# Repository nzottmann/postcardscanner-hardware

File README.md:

## Hardware files for postcardscanner

License: CC-BY-SA-4.0

- 3D CAD, Fusion360 and STEP
- 3D printing files, 3MF
- Hardware BOM
- KiCAD files for custom PCB
- Pictures

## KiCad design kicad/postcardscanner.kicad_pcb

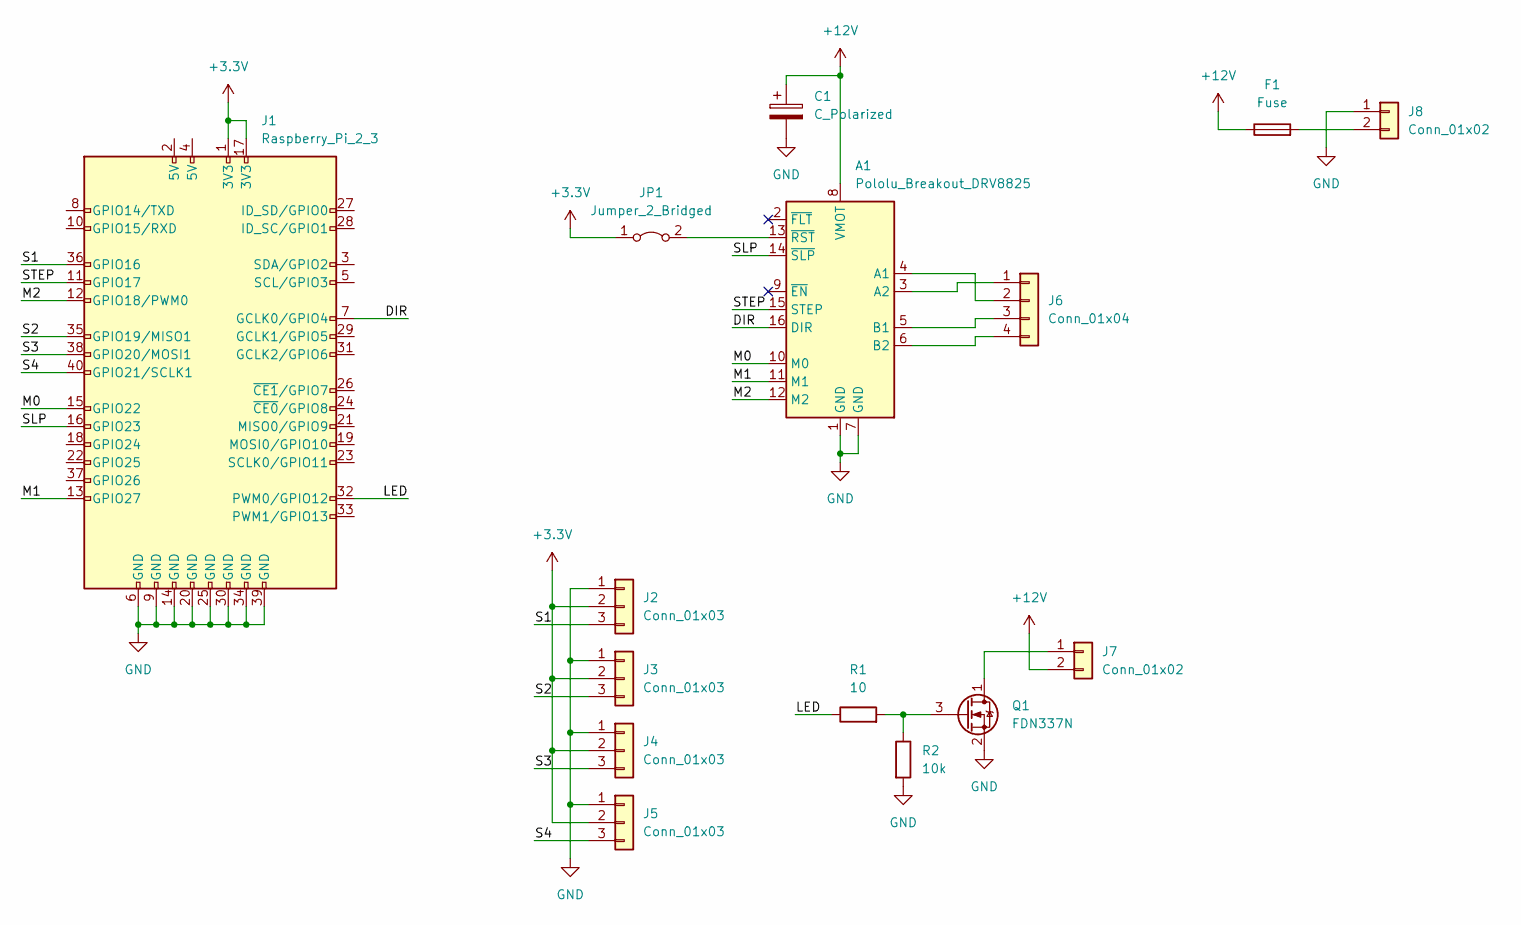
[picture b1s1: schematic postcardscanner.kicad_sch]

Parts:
A1: Pololu_Breakout_DRV8825; Pololu_Breakout-16_15.2x20.3mm
C1: C_Polarized; CP_Radial_D8.0mm_P5.00mm
F1: Fuse; Fuseholder_Littelfuse_445_030_series_5x20mm
J1: Raspberry_Pi_2_3; PinSocket_2x20_P2.54mm_Vertical
J2, J3, J4, J5: Conn_01x03; SolderWire-0.25sqmm_1x03_P4.2mm_D0.65mm_OD1.7mm_Relief
J6: Conn_01x04; SolderWire-0.25sqmm_1x04_P4.2mm_D0.65mm_OD1.7mm_Relief
J7: Conn_01x02; SolderWire-0.25sqmm_1x02_P4.2mm_D0.65mm_OD1.7mm_Relief
J8: Conn_01x02; SolderWire-0.5sqmm_1x02_P4.6mm_D0.9mm_OD2.1mm_Relief
JP1: Jumper_2_Bridged; SolderJumper-2_P1.3mm_Bridged_RoundedPad1.0x1.5mm
Q1: FDN337N; SOT-23_Handsoldering
R1: 10; R_0603_1608Metric_Pad0.98x0.95mm_HandSolder
R2: 10k; R_0603_1608Metric_Pad0.98x0.95mm_HandSolder

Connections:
+3.3V: J1.1 (3V3), J1.17 (3V3), J2.2, J3.2, J4.2, J5.2, JP1.1 (A)
+12V: A1.8 (VMOT), C1.1, F1.1, J7.2
/DIR: A1.16 (DIR), J1.7 (GCLK0/GPIO4)
/LED: J1.32 (PWM0/GPIO12), R1.1
/M0: A1.10 (M0), J1.15 (GPIO22)
/M1: A1.11 (M1), J1.13 (GPIO27)
/M2: A1.12 (M2), J1.12 (GPIO18/PWM0)
/S1: J1.36 (GPIO16), J2.3
/S2: J1.35 (GPIO19/MISO1), J3.3
/S3: J1.38 (GPIO20/MOSI1), J4.3
/S4: J1.40 (GPIO21/SCLK1), J5.3
/SLP: A1.14 (~SLP), J1.16 (GPIO23)
/STEP: A1.15 (STEP), J1.11 (GPIO17)
GND: A1.1 (GND), A1.7 (GND), C1.2, J1.6 (GND), J1.9 (GND), J1.14 (GND), J1.20 (GND), J1.25 (GND), J1.30 (GND), J1.34 (GND), J1.39 (GND), J2.1, J3.1, J4.1, J5.1, J8.1, Q1.2 (S), R2.2
unnamed: A1.3 (A2), J6.1
unnamed: A1.4 (A1), J6.2
unnamed: A1.5 (B1), J6.3
unnamed: A1.6 (B2), J6.4
unnamed: A1.13 (~RST), JP1.2 (B)
unnamed: F1.2, J8.2
unnamed: J7.1, Q1.1 (D)
unnamed: Q1.3 (G), R1.2, R2.1

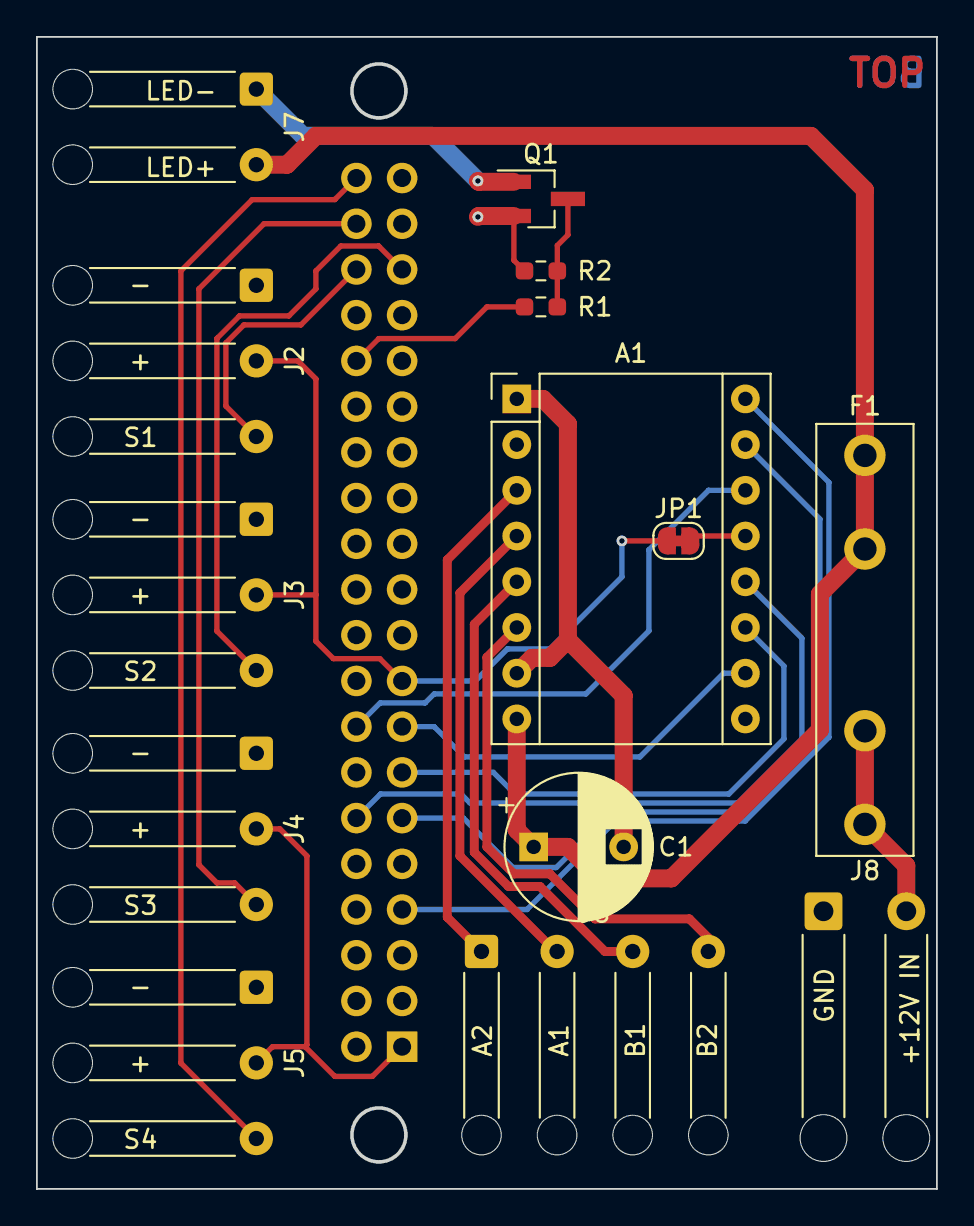
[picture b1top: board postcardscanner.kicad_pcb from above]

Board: 2 copper layers, 49.9 x 63.9 mm, 15 parts (1 on the bottom side), 22 nets.

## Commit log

2022-12-04 Add pictures to readme
